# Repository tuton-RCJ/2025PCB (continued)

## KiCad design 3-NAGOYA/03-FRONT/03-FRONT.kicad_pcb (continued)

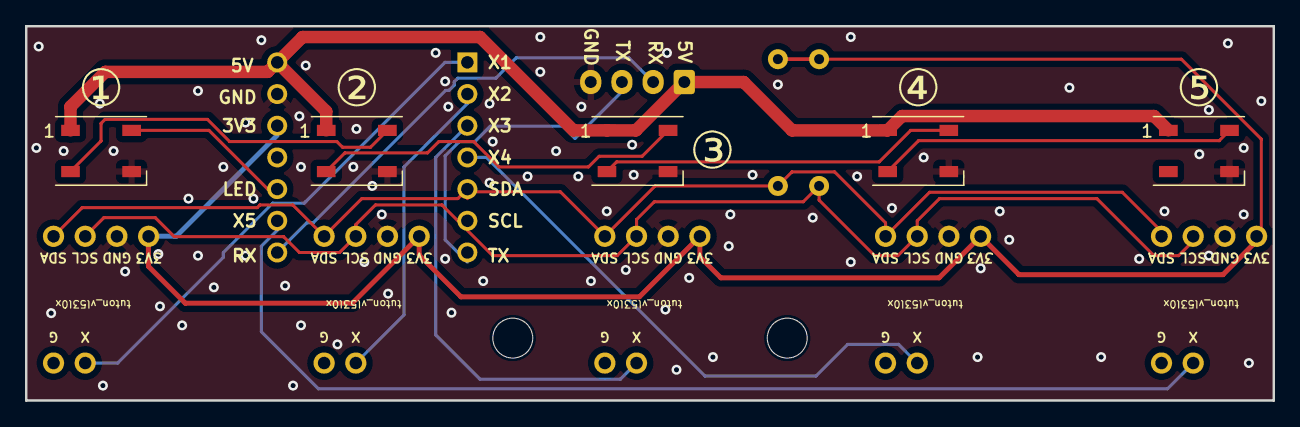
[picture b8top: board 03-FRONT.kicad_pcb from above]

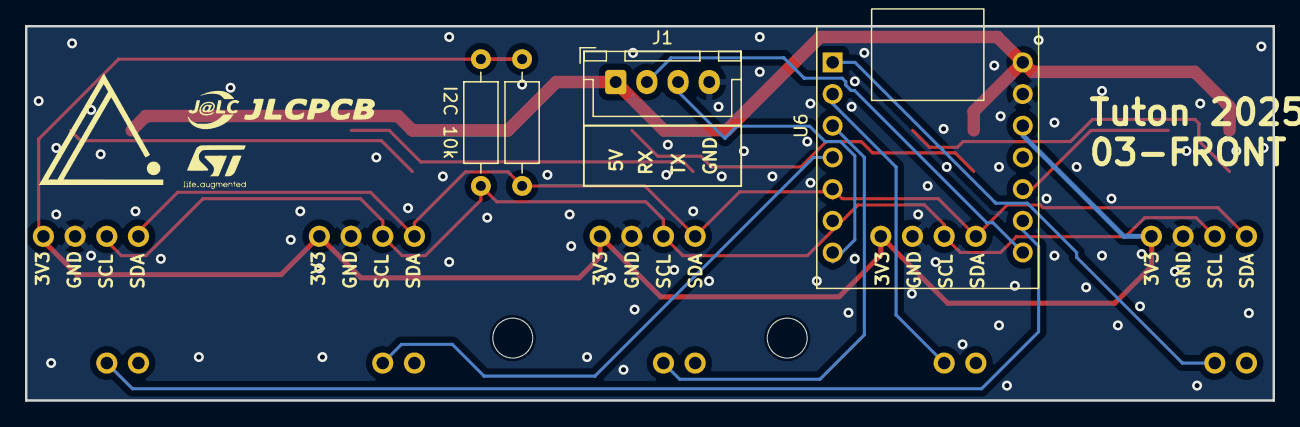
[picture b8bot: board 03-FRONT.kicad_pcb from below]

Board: 2 copper layers, 100.0 x 30.0 mm, 16 parts (4 on the bottom side), 17 nets.

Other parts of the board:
J1: OpenMV Conn; JST_XH_B4B-XH-A_1x04_P2.50mm_Vertical

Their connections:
+5V: J1.1; also elsewhere on the board
GND: J1.4; also elsewhere on the board
RX: J1.2; also elsewhere on the board
TX: J1.3; also elsewhere on the board

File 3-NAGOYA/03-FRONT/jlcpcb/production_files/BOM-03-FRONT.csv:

Comment,Designator,Footprint,LCSC
MountingHole,H2,MountingHole_3.2mm_M3,
WS2812B,D1,LED_WS2812B_PLCC4_5.0x5.0mm_P3.2mm,
~,U5,VL53L0X_horizontal,
WS2812B,D4,LED_WS2812B_PLCC4_5.0x5.0mm_P3.2mm,
WS2812B,D2,LED_WS2812B_PLCC4_5.0x5.0mm_P3.2mm,
~,U2,VL53L0X_horizontal,
WS2812B,D5,LED_WS2812B_PLCC4_5.0x5.0mm_P3.2mm,
MountingHole,H1,MountingHole_3.2mm_M3,
~,U4,VL53L0X_horizontal,
WS2812B,D3,LED_WS2812B_PLCC4_5.0x5.0mm_P3.2mm,
~,U3,VL53L0X_horizontal,
~,U1,VL53L0X_horizontal,
10k,R1,R_Axial_DIN0207_L6.3mm_D2.5mm_P10.16mm_Horizontal,
OpenMV Conn,J1,JST_XH_B4B-XH-A_1x04_P2.50mm_Vertical,
10k,R2,R_Axial_DIN0207_L6.3mm_D2.5mm_P10.16mm_Horizontal,
~,U6,MOUDLE14P-2.54-21X17.8MM,

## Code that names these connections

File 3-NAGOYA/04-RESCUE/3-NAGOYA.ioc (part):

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Mcu.Name=STM32F103R(C-D-E)Tx
Mcu.Package=LQFP64
Mcu.UserName=STM32F103RCTx
PA0-WKUP.Signal=S_TIM2_CH1_ETR
PA1.Signal=S_TIM2_CH2
PA10.Mode=Asynchronous
PA10.Signal=USART1_RX
PA11.Signal=S_TIM1_CH4
PA14.Signal=GPIO_Output
PA15.Signal=GPIO_Output
PA2.Mode=Asynchronous
PA2.Signal=USART2_TX
PA3.Mode=Asynchronous
PA3.Signal=USART2_RX
PA6.Signal=S_TIM3_CH1
PA8.Signal=S_TIM1_CH1
PA9.Mode=Asynchronous
PA9.Signal=USART1_TX
PB10.Mode=Asynchronous
PB10.Signal=USART3_TX
PB11.Mode=Asynchronous
PB11.Signal=USART3_RX
PB15.Signal=GPIO_Output
PB6.Mode=I2C
PB6.Signal=I2C1_SCL
PB7.Mode=I2C
PB7.Signal=I2C1_SDA
PC0.Signal=ADCx_IN10
PC1.Signal=ADCx_IN11
PC10.Mode=Asynchronous
PC10.Signal=UART4_TX
PC11.Mode=Asynchronous
PC11.Signal=UART4_RX
board=custom

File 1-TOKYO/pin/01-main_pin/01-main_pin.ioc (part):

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Mcu.Name=STM32F446R(C-E)Tx
Mcu.Package=LQFP64
Mcu.UserName=STM32F446RETx
PA0-WKUP.Mode=Asynchronous
PA0-WKUP.Signal=UART4_TX
PA1.Mode=Asynchronous
PA1.Signal=UART4_RX
PA10.Mode=Asynchronous
PA10.Signal=USART1_RX
PA11.Signal=S_TIM1_CH4
PA2.Mode=Asynchronous
PA2.Signal=USART2_TX
PA3.Mode=Asynchronous
PA3.Signal=USART2_RX
PA5.Signal=S_TIM2_CH1_ETR
PA6.Signal=S_TIM3_CH1
PA7.Signal=S_TIM3_CH2
PA8.Signal=S_TIM1_CH1
PA9.Mode=Asynchronous
PA9.Signal=USART1_TX
PB0.Signal=S_TIM3_CH3
PB1.Signal=S_TIM3_CH4
PB10.Mode=I2C
PB10.Signal=I2C2_SCL
PB3.Mode=I2C
PB3.Signal=I2C2_SDA
PB8.Mode=I2C
PB8.Signal=I2C1_SCL
PB9.Mode=I2C
PB9.Signal=I2C1_SDA
PC0.Signal=ADCx_IN10
PC1.Signal=ADCx_IN11
PC10.Mode=Asynchronous
PC10.Signal=USART3_TX
PC12.Mode=Asynchronous
PC12.Signal=UART5_TX
PC5.Mode=Asynchronous
PC5.Signal=USART3_RX
PC6.Mode=Asynchronous
PC6.Signal=USART6_TX
PC7.Mode=Asynchronous
PC7.Signal=USART6_RX
PD2.Mode=Asynchronous
PD2.Signal=UART5_RX
board=custom

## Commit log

2024-02-23 add main
2024-02-23 readme
2024-03-20 祝日は進捗を生む日
2024-03-20 基板は5つだぜ
2024-03-22 全国行きたかった
2024-04-28 がんばる
2024-04-28 基板は6つ
2024-05-06 line...
2024-05-07 ラインセンサ完成
2024-05-07 前けずった
2024-06-23 いっぱい増えた
2024-11-24 KANTOプロジェクト始動
2024-12-10 作ってる
2024-12-19 mike
2025-01-05 Create notify_push
    send a message to discord
2025-01-05 かんぺきなきばん
2025-01-05 lalala
2025-01-05 waiwai
2025-01-13 NAGOYA機設計開始
2025-01-13 FRONT回路設計終わった
2025-01-13 03-FRONT部品割り当て終わり
2025-01-13 03-FRONT部品配置終わり
2025-01-13 05-PWR回路設計完了
2025-01-13 03-FRONT 3Dモデル出力
2025-01-17 01-MAIN回路図終わり
2025-01-19 03-FRONT XIAOに変更
2025-01-19 06-UI完成
2025-01-23 01-MAIN部品配置完了
2025-01-26 01-MAIN基板設計完了
2025-01-28 04-RESCUE完了。全基板あとシルクだけ
2025-02-06 つかれた
